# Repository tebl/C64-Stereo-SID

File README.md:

# C64 Stereo SID

There are many Stereo SID boards out there, but this one is mine - mostly because I did not feel like tracking down or paying premium to get one of those wirewrap sockets. Using a simple board like this will put a second SID chip at $DE00 and add 3 voices to your system, with suitable software and a selection of SID files you can play music on your system like never experienced before (your mileage may vary)! For everyday use you can use it in pseudo stereo-mode by having each SID play the same thing simultaniously.

As with anything dealing with SID chips you should know what you are doing, this board does not deal with the specific power requirements used between SID types and putting the wrong thing in there will certainly kill the chip you value the most or both of them! Personally I built the board with the intention of using it with substitutes like SwinSID, SwinSID Ultimate and ARMsid and all those should be perfectly safe to use in any combination (that way you don't deprive a C64 of its audio qualities).

The stock computer does not have any way of connecting up the audio from the second SID, the standard A/V cables are naturally mono as that is what the system was designed to be. This means you'll need to add relevant connectors to your system such as RCA sockets, either in the form of custom-made cables hanging out the back or by drilling and adding the connectors to your case (please don't drill into a case and expect me to buy it later). A third option is to replace the modulator with one that adds something like a 3.5mm stereo audio connector, which is what I did with my other PCB for [C64-Modulator-Replacement](https://github.com/tebl/C64-Modulator-Replacement).

## Building the board
Soldering together the few components should be easy going as long as you have access to reasonable tools, personally I'm using a cheap soldering station with adjustable temperature so no need to go expensive if you don't have to. Use 60/40 soldering tin, the lead free makes to job a lot harder if you're new to the hobby.

Start by studying the PCB, both sides and perform dry fits to see that you have an idea of where everything goes since removing things is always a lot harder than getting it right in the first place (match orientation to symbols, see gallery images for reference).

With a lot going on for such a tiny board, you'd need to pay some attention to the sequence of components getting soldered in. The list below is the one I recommend, note that with some sockets you'll have less space underneath and it'll be a lot easier getting it into place if you trim the pins after they have been soldered into place. When aligning the two 14-pin (round) pin-headers I recommend using a round-pin socket to help keep them straight, that way you won't get issues trying to install it into the Commodore 64.

1. Check errata below
2. Resistors, see note on dowmixing below.
2. 14 pin-headers on the marked A1 as well as a similar one on the right side (solder on reverse-side). Refer to [this image](https://raw.githubusercontent.com/tebl/C64-Stereo-SID/master/gallery/2019-07-30%2016.36.22.jpg) for reference.
3. Sockets for U1/U2
4. Capacitors according to values on silkscreen, note the different value for C70/C71 according to the type of SID chips that belong in the system you are installing it.
5. Remaining components

### Downmixing
The board has components for downmixing the audio coming out of both SID chips down to a mono signal, via the installation of two resistors - R2 and R3. If you want your stereo to be in, well - stereo - then the suggested route is installing a wire in place of R2 and leaving the spot for R3 blank.  

### Errata
- Revision B has a missing trace between the top of R1 and the bottom of D1, you can add a wire between them to restore functionality when using two chips in pseudo-stereo mode. For reference, the missing wire is the only green wire in the following [picture](https://github.com/tebl/C64-Stereo-SID/raw/master/gallery/revision_b_fix.PNG). 

## Installing the board
The board should slot nicely into the existing socket for the previous SID, this is removed and usually installed as the primary SID on the Stereo SID board. There may be components such as capacitors that interfere with the new board, take care to examine and gently bend away those that are in the way before firmly pushing it into the socket.

Below you can see a picture of the board installed in one of the classic breadbins, without the "breadbin"-part at the moment. Here I have the 6581 installed as my primary SID chip, the rather excellent ARMsid is installed as my secondary chip and is available at $DE00 given the default installation of the CS-wire (white) going to seventh pin of the cartridge expansion port (counted from the left). The audio output of the second SID (green) has been routed to the stereo audio jack on my system though, as already discussed in the introduction, you may opt for something else entirely.

Note the 3-pin header pins, designated EXT_IN_SEL1 and EXT_IN_SEL2 - these connect up the audio coming into the system on the standard A/V cables. I usually leave these unjumpered in order to avoid mixing stray noise into the outgoing sound, but some people like to have these connected straight to ground by jumpering across pins 2-3. When using equipment expecting the SID to mix in externally generated audio such as the Currah uSpeech, jumper the primary SID to pins 1-2.

## Using the board
Given that most software don't know how or even where to look for a Secondary SID, you don't immediately get stereo sound on your system - the software need to have this functionality added to it. There is a great page at [lyonlabs.org/commodore/stereo-sid](https://www.lyonlabs.org/commodore/stereo-sid/) with a wealth of information on how to get going with it, I recommend starting with StereoPlayer 10.2 as part of the section called "Playing Stereo SIDs" as that is the one I ended up using with this board (also comes with a few sample steareo SID-files).

Press the Commodore-key to change StereoPlayer configuration, press A to cycle **address** to $DE00 and push M to change **mode** to stereo. Personally I also had to turn **Fast Load** off before loading files as I was not using a fastloader cartridge with my [Pi1541](https://github.com/tebl/C64-Pi1541-Module), this stopped a few of the issues I was having when listing disk contents and loading music files. Press the "<--"-key to save configuration for later, the Commodore-key returns you to the menu. Select a Stereo SID file from the list and add it to the list to play them - I had some isssues with some files that were not recognized, so I found that not using the play all button worked best for me.

Other than that, enjoy the glorious feeling of playing those Stereo SID files on the Commodore 64!

# Schematic
The supplied KiCad files should be sufficient as both a schematic and as a  starting point for ordering PCBs (basically you could just zip the contents of the export folder and upload that on a fabrication site), the schematic is also available in [PDF-format](https://github.com/tebl/C64-Stereo-SID/raw/master/export/C64%20Stereo%20SID.pdf) and this is what you'll need to print and work your way through this things don't work as expected after assembly.

# BOM
Most parts should be easy to get a hold of from your favourite local electronic component shop, but given that I don't have access to such shops where I live so everything was based on whatever I could get cheapest from ebay/AliExpress (free shipping, plan on usually waiting 3-4 weeks though). The list below should be everything you'll need in addition to a workable soldering iron and some 60/40 soldering tin.

Pin headers you order in bulk and snap off parts as needed, but note that you should get round pin headers for the part that goes into the socket - while you can use the regular kind if needed, you may easily wear out or end up breaking the socket. Relevant part details have also been added to the PCB itself.

| Reference    | Item                                  | Count |
| ------------ | ------------------------------------- | ----- |
| PCB          | Fabricate using Gerber files ([order](https://www.pcbway.com/project/shareproject/Commodore_64_Stereo_SID.html?inviteid=88707))          |     1 |
| C70/C71**   | 470pF (6581) or 22nF (8580) capacitor |     2 |
| C74         | 1000pF capacitor                      |     1 |
| C76         | 470pF capacitor                       |     1 |
| C77         | 10uF electrolytic capacitor           |     1 |
| D1, D2      | 1N4148 small signal diode             |     2 |
| J1-J3       | 3-pin straight header                 |     3 |
| J4          | 2-pin straight header                 |     1 |
| R1,R12      | 1k ohm resistor                       |     2 | 
| R2          | Install wire for standard stereo      |   (1) |
| R2, R3      | 1k ohm resistor (downmix to mono)     |   (2) |
| R8*         | 1k ohm resistor                       |   (1) | 
| R9          | 10k ohm resistor                      |     1 | 
| Q1          | 2N2222 transistor (TO-92)             |     1 |
| A1          | 14-pin round pin header               |     2 |
| U1, U2      | 28-pin wide socket                    |     2 |

\* R8 - not installed on motherboards that use 8580 SID chips 

** C70/C71 - Install either both 470pF for motherboards supporting 6581, 22nF for motherboards supporting 8580.

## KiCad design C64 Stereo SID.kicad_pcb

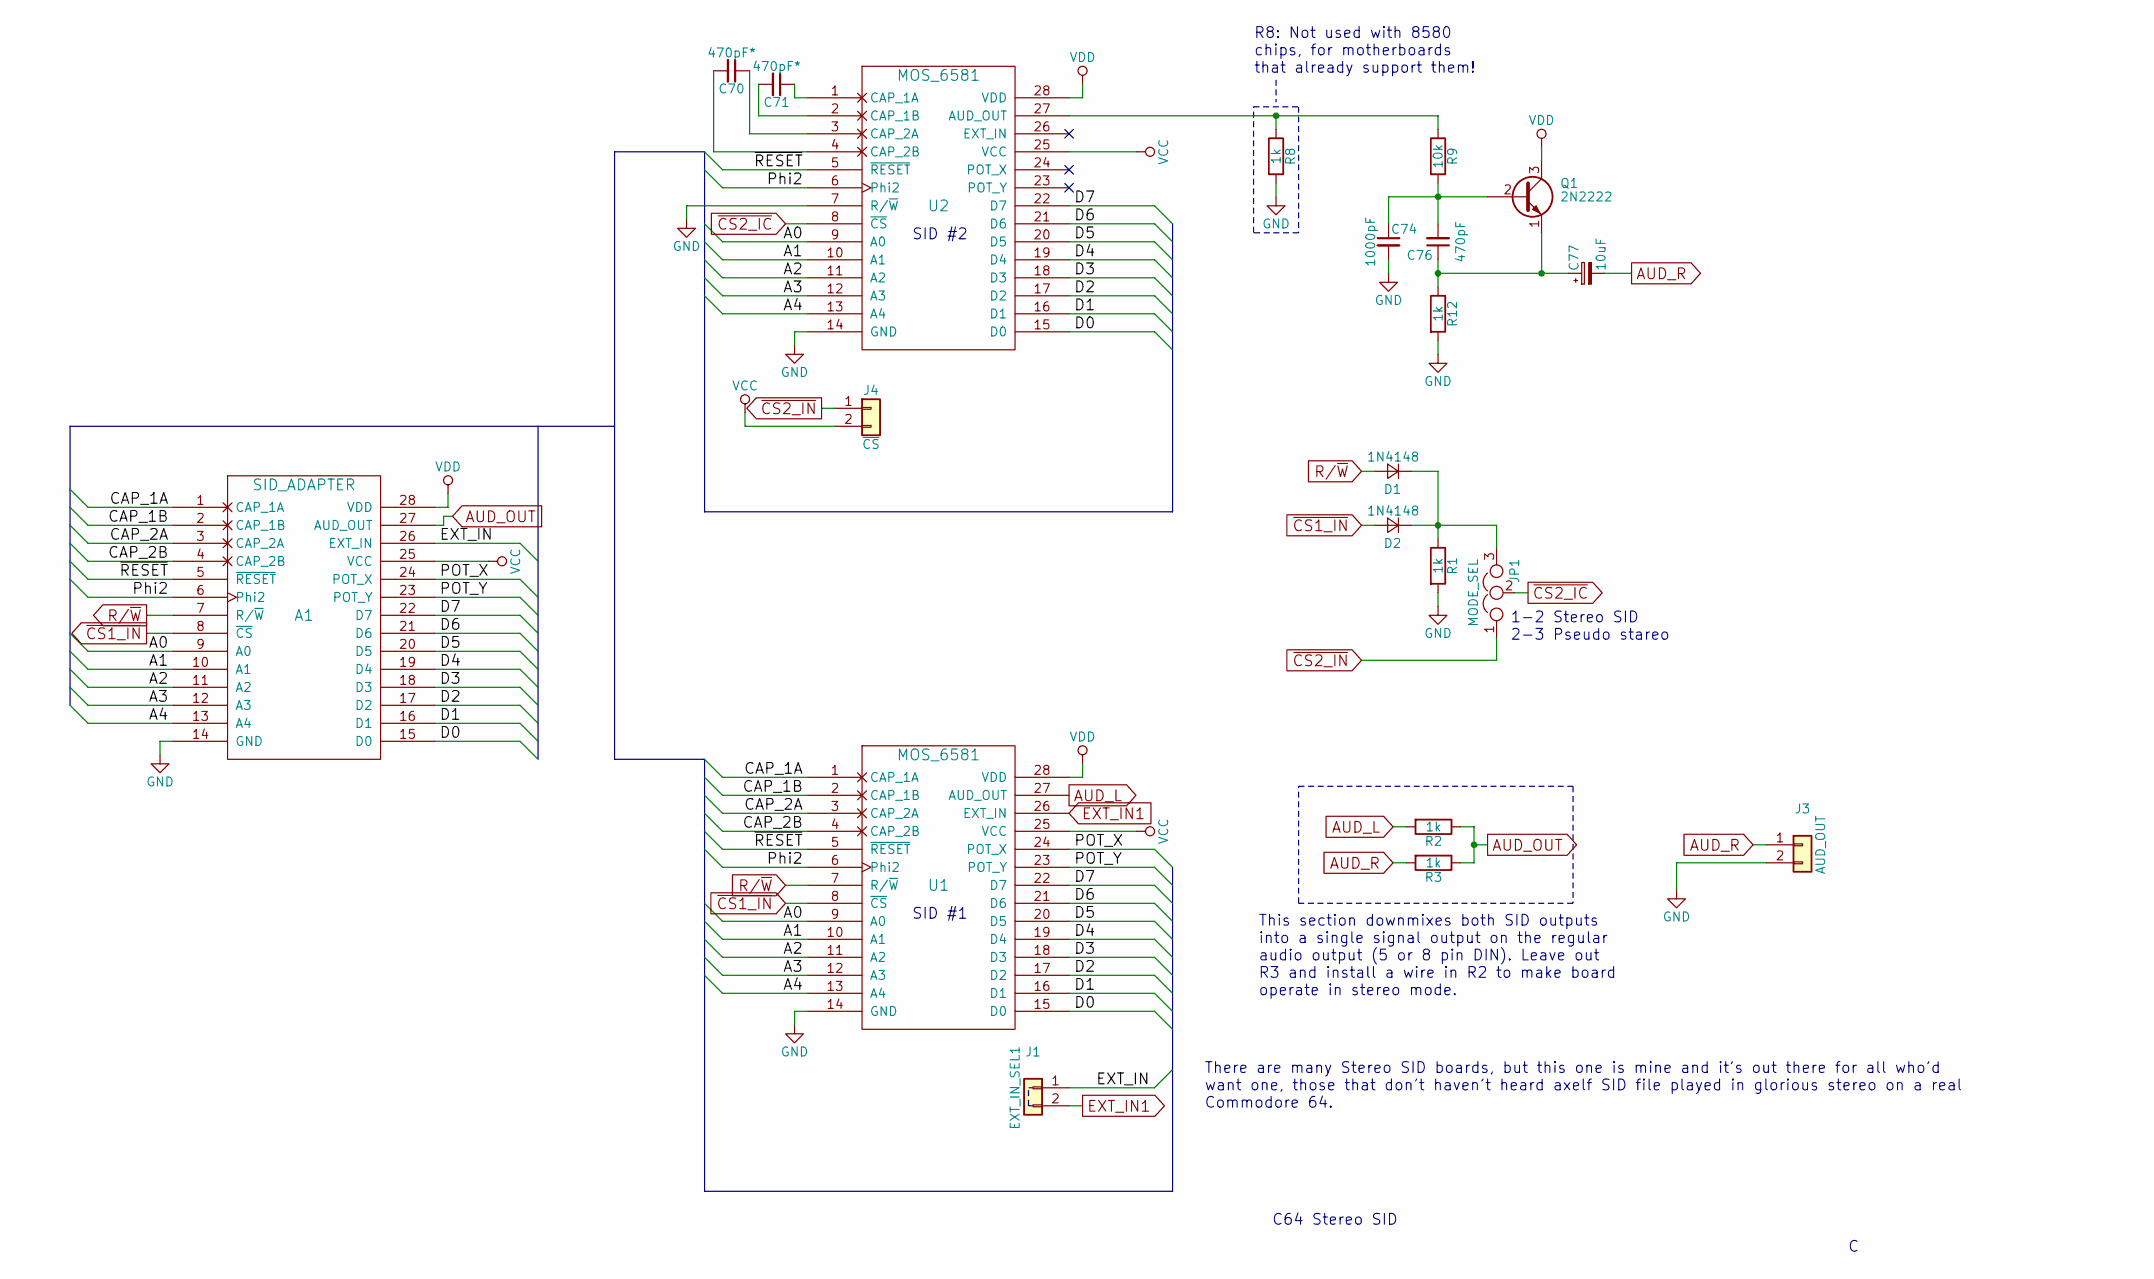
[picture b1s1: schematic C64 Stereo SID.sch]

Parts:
A1: SID_ADAPTER; MOS_6581_Adapter
C70, C71: 470pF*; C_Disc_D4.7mm_W2.5mm_P5.00mm
C74: 1000pF; C_Disc_D4.7mm_W2.5mm_P5.00mm
C76: 470pF; C_Disc_D4.7mm_W2.5mm_P5.00mm
C77: 10uF; CP_Radial_D4.0mm_P2.00mm
D1, D2: 1N4148; D_DO-35_SOD27_P7.62mm_Horizontal
J1: EXT_IN_SEL1; Pin_Header_Straight_1x02_Pitch2.54mm
J3: AUD_OUT; Pin_Header_Straight_1x02_Pitch2.54mm
J4: ~CS; Pin_Header_Straight_1x02_Pitch2.54mm
JP1: MODE_SEL; Pin_Header_Straight_1x03_Pitch2.54mm
Q1: 2N2222; TO-92_Molded_Narrow
R1, R2, R3, R8, R12: 1k; R_Axial_DIN0207_L6.3mm_D2.5mm_P10.16mm_Horizontal
R9: 10k; R_Axial_DIN0207_L6.3mm_D2.5mm_P10.16mm_Horizontal
U1, U2: MOS_6581; DIP-28_W15.24mm_Socket

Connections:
/A0: A1.9 (A0), U1.9 (A0), U2.9 (A0)
/A1: A1.10 (A1), U1.10 (A1), U2.10 (A1)
/A2: A1.11 (A2), U1.11 (A2), U2.11 (A2)
/A3: A1.12 (A3), U1.12 (A3), U2.12 (A3)
/A4: A1.13 (A4), U1.13 (A4), U2.13 (A4)
/CAP_1A: A1.1 (CAP_1A), U1.1 (CAP_1A)
/CAP_1B: A1.2 (CAP_1B), U1.2 (CAP_1B)
/CAP_2A: A1.3 (CAP_2A), U1.3 (CAP_2A)
/CAP_2B: A1.4 (CAP_2B), U1.4 (CAP_2B)
/D0: A1.15 (D0), U1.15 (D0), U2.15 (D0)
/D1: A1.16 (D1), U1.16 (D1), U2.16 (D1)
/D2: A1.17 (D2), U1.17 (D2), U2.17 (D2)
/D3: A1.18 (D3), U1.18 (D3), U2.18 (D3)
/D4: A1.19 (D4), U1.19 (D4), U2.19 (D4)
/D5: A1.20 (D5), U1.20 (D5), U2.20 (D5)
/D6: A1.21 (D6), U1.21 (D6), U2.21 (D6)
/D7: A1.22 (D7), U1.22 (D7), U2.22 (D7)
/EXT_IN: A1.26 (EXT_IN), J1.1
/POT_X: A1.24 (POT_X), U1.24 (POT_X)
/POT_Y: A1.23 (POT_Y), U1.23 (POT_Y)
/Phi2: A1.6 (Phi2), U1.6 (Phi2), U2.6 (Phi2)
/~RESET: A1.5 (~RESET), U1.5 (~RESET), U2.5 (~RESET)
AUD_L: R2.2, U1.27 (AUD_OUT)
AUD_OUT: A1.27 (AUD_OUT), R2.1, R3.1
AUD_R: C77.2, J3.1, R3.2
EXT_IN1: J1.2, U1.26 (EXT_IN)
GND: A1.14 (GND), C74.2, J3.2, R1.2, R8.2, R12.2, U1.14 (GND), U2.7 (R/~W), U2.14 (GND)
unnamed: C70.1, U2.3 (CAP_2A)
unnamed: C70.2, U2.4 (CAP_2B)
unnamed: C71.1, U2.1 (CAP_1A)
unnamed: C71.2, U2.2 (CAP_1B)
unnamed: C74.1, C76.2, Q1.2 (B), R9.2
unnamed: C76.1, C77.1, Q1.1 (E), R12.1
unnamed: D1.1 (K), D2.1 (K), JP1.3, R1.1
unnamed: R8.1, R9.1, U2.27 (AUD_OUT)
R/~W: A1.7 (R/~W), D1.2 (A), U1.7 (R/~W)
VCC: A1.25 (VCC), J4.2, U1.25 (VCC), U2.25 (VCC)
VDD: A1.28 (VDD), Q1.3 (C), U1.28 (VDD), U2.28 (VDD)
~CS1_IN: A1.8 (~CS), D2.2 (A), U1.8 (~CS)
~CS2_IC: JP1.2, U2.8 (~CS)
~CS2_IN: J4.1, JP1.1

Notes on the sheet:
SID #2
SID #1
R8: Not used with 8580 chips, for motherboards that already support them!
This section downmixes both SID outputs into a single signal output on the regular audio output (5 or 8 pin DIN). Leave out R3 and install a wire in R2 to make board operate in stereo mode.
C64 Stereo SID
There are many Stereo SID boards, but this one is mine and it's out there for all who'd want one, those that don't haven't heard axelf SID file played in glorious stereo on a real Commodore 64.
1-2 Stereo SID 2-3 Pseudo stareo

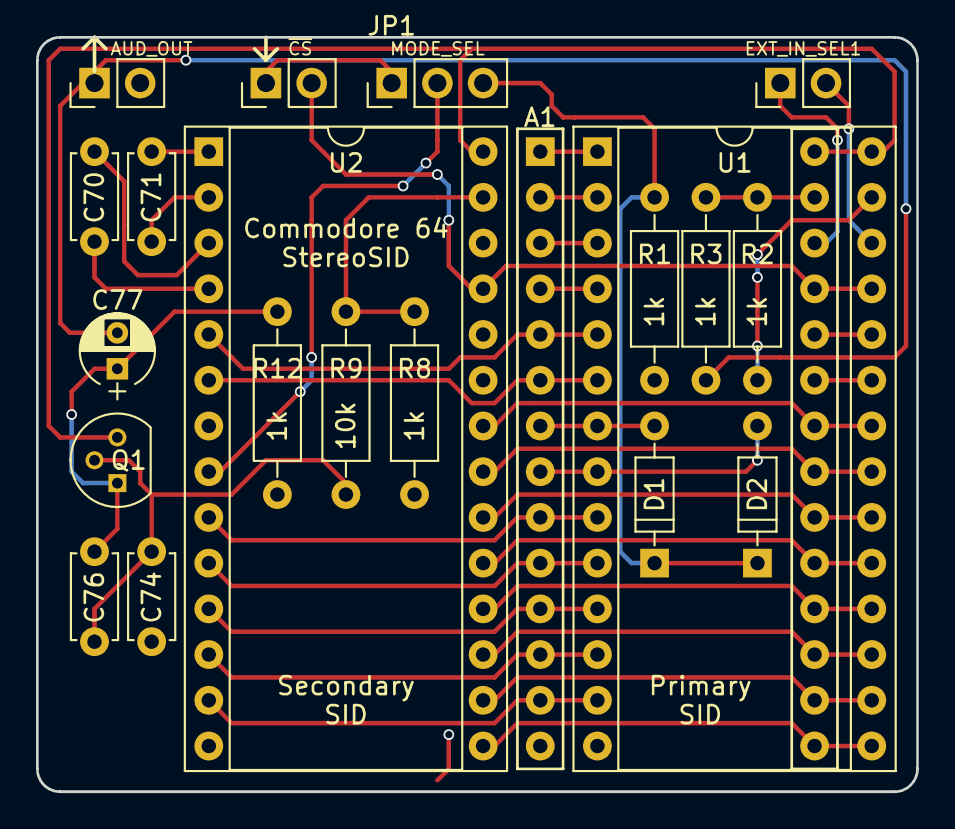
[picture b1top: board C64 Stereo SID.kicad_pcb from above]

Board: 2 copper layers, 48.9 x 41.9 mm, 21 parts (0 on the bottom side), 41 nets.

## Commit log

2019-06-30 Board picture
2019-06-30 Added schematic
2019-06-30 Assigned footprints
2019-07-01 Tracks routed and silkscreen added
2019-07-01 Gerber exports
2019-07-01 Added header for swapping SIDs around
2019-08-07 Changed to select SIDs as pseudo stereo
2019-08-07 Gerber export
2019-08-17 Added simple README
2019-08-20 Updated gerbers and added images
2019-09-10 Updated README with build and usage details
2019-10-07 Revision B errata picture
2019-10-07 Fixed missing trace on the revision B boards
2019-10-08 Revised pin headers brought out
